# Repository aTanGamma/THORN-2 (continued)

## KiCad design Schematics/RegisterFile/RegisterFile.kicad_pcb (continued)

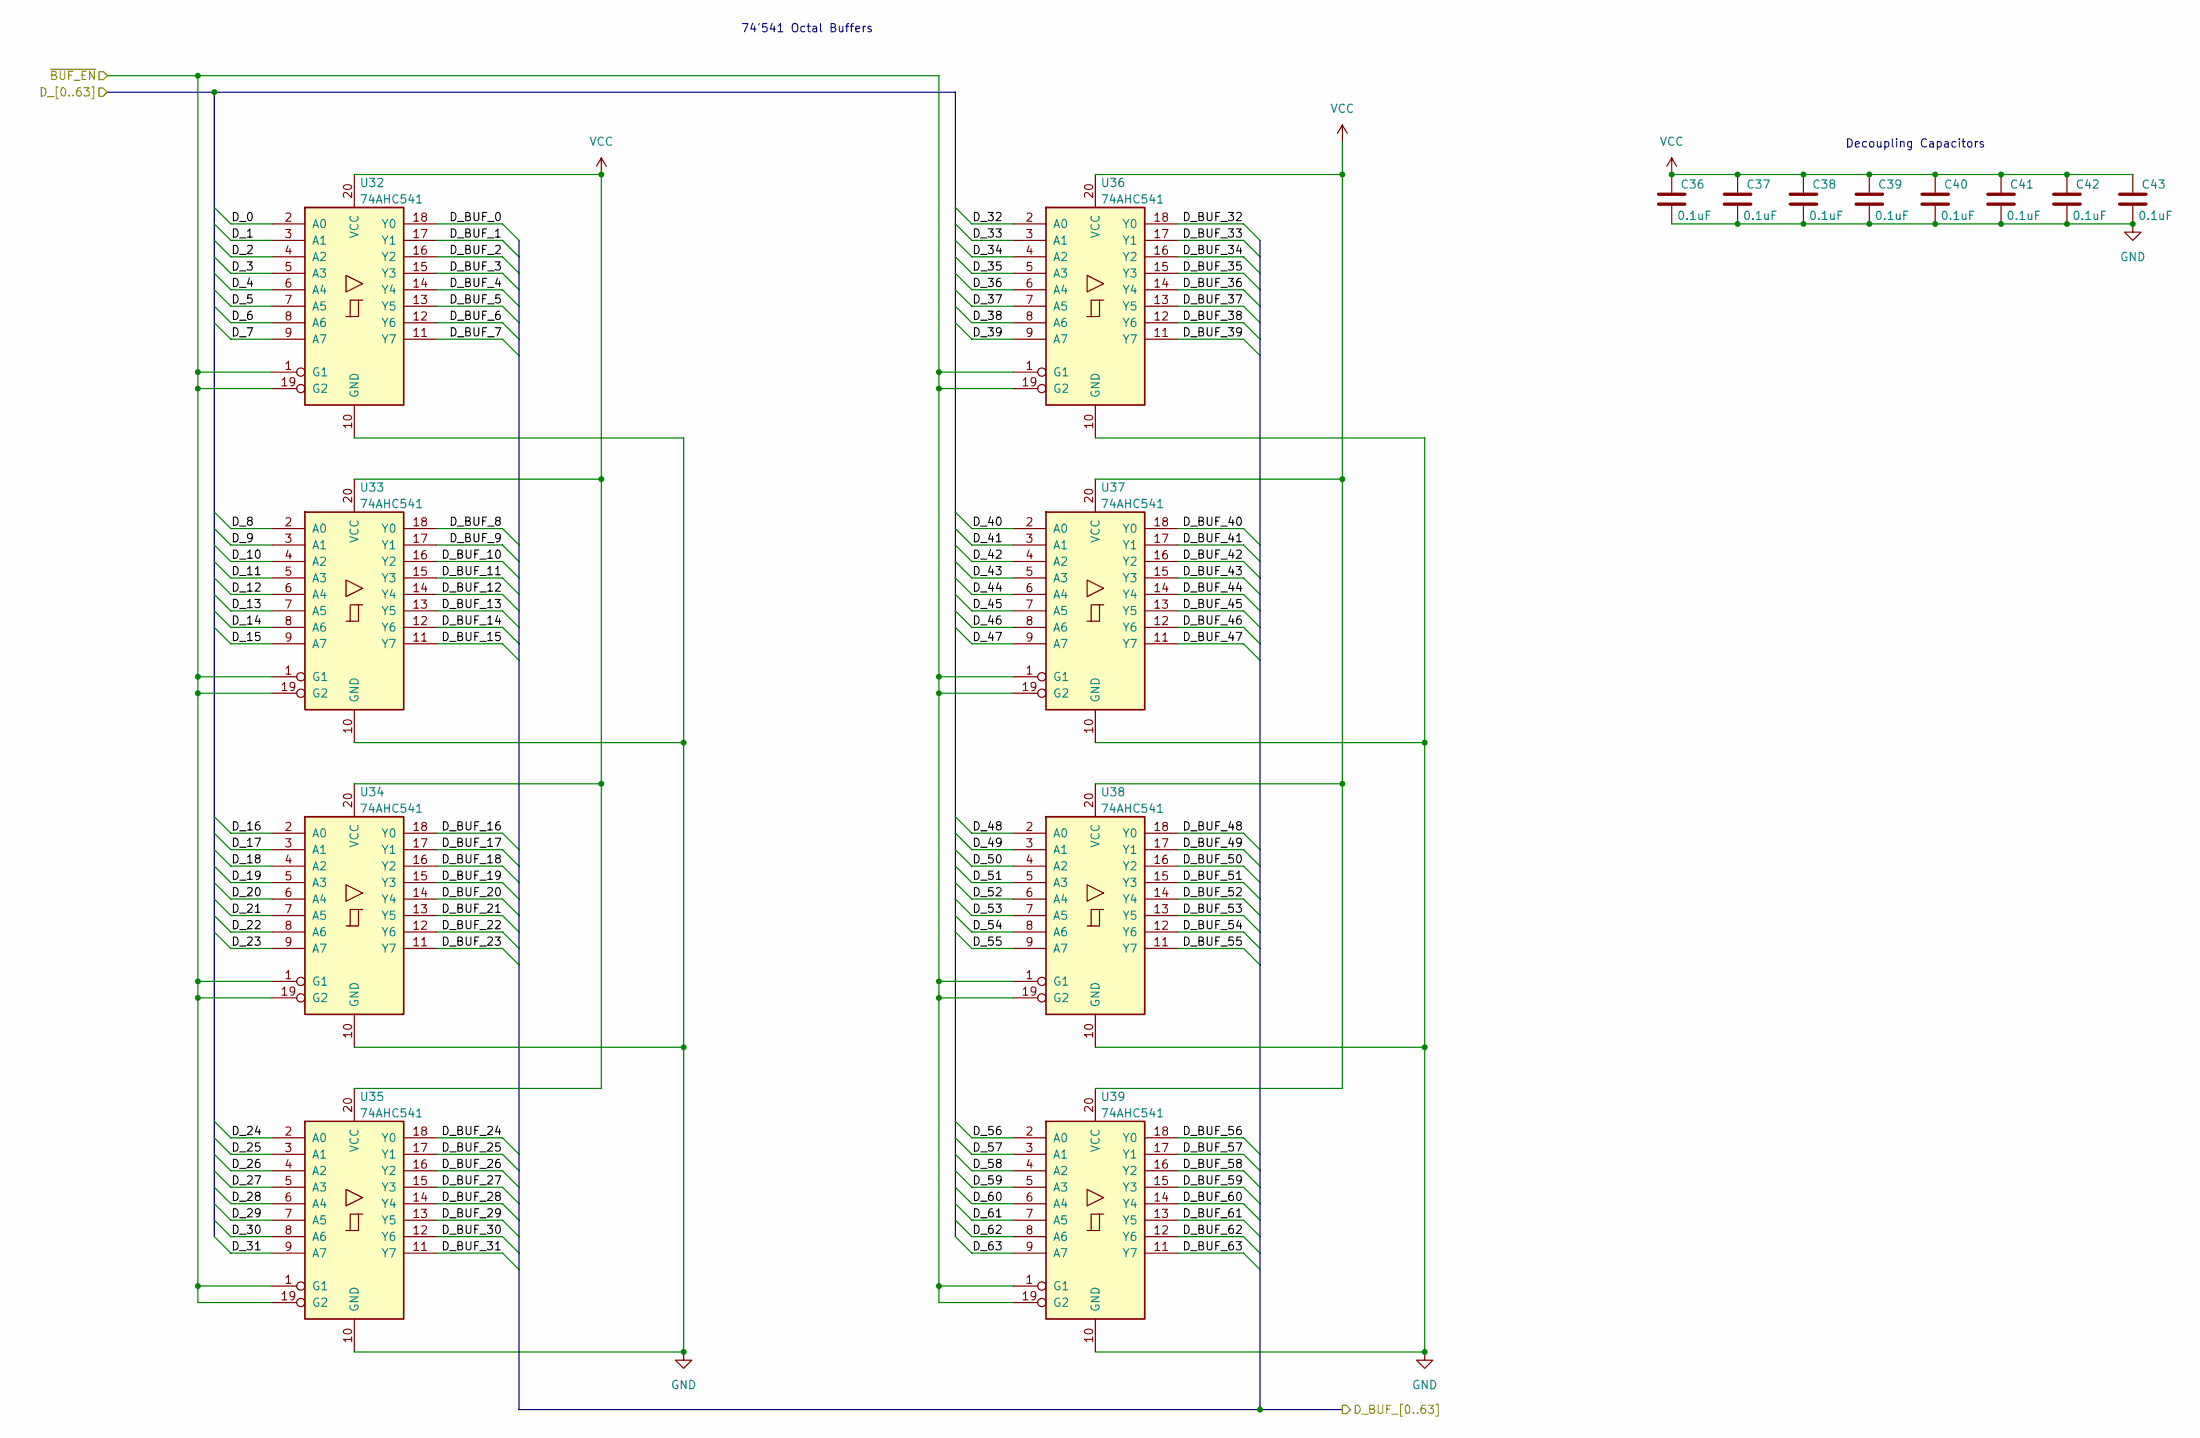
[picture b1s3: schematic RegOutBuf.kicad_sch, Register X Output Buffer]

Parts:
C36, C37, C38, C39, C40, C41, C42, C43: 0.1uF; C_1206_3216Metric
U32, U33, U34, U35, U36, U37, U38, U39: 74AHC541; TSSOP-20_4.4x6.5mm_P0.65mm

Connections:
/Register_RAM_Bank_Y/Data_0: U32.18 (Y0); also elsewhere on the board
/Register_RAM_Bank_Y/Data_1: U32.17 (Y1); also elsewhere on the board
/Register_RAM_Bank_Y/Data_2: U32.16 (Y2); also elsewhere on the board
/Register_RAM_Bank_Y/Data_3: U32.15 (Y3); also elsewhere on the board
/Register_RAM_Bank_Y/Data_4: U32.14 (Y4); also elsewhere on the board
/Register_RAM_Bank_Y/Data_5: U32.13 (Y5); also elsewhere on the board
/Register_RAM_Bank_Y/Data_6: U32.12 (Y6); also elsewhere on the board
/Register_RAM_Bank_Y/Data_7: U32.11 (Y7); also elsewhere on the board
/Register_RAM_Bank_Y/Data_8: U33.18 (Y0); also elsewhere on the board
/Register_RAM_Bank_Y/Data_9: U33.17 (Y1); also elsewhere on the board
/Register_RAM_Bank_Y/Data_10: U33.16 (Y2); also elsewhere on the board
/Register_RAM_Bank_Y/Data_11: U33.15 (Y3); also elsewhere on the board
/Register_RAM_Bank_Y/Data_12: U33.14 (Y4); also elsewhere on the board
/Register_RAM_Bank_Y/Data_13: U33.13 (Y5); also elsewhere on the board
/Register_RAM_Bank_Y/Data_14: U33.12 (Y6); also elsewhere on the board
/Register_RAM_Bank_Y/Data_15: U33.11 (Y7); also elsewhere on the board
/Register_RAM_Bank_Y/Data_16: U34.18 (Y0); also elsewhere on the board
/Register_RAM_Bank_Y/Data_17: U34.17 (Y1); also elsewhere on the board
/Register_RAM_Bank_Y/Data_18: U34.16 (Y2); also elsewhere on the board
/Register_RAM_Bank_Y/Data_19: U34.15 (Y3); also elsewhere on the board
/Register_RAM_Bank_Y/Data_20: U34.14 (Y4); also elsewhere on the board
/Register_RAM_Bank_Y/Data_21: U34.13 (Y5); also elsewhere on the board
/Register_RAM_Bank_Y/Data_22: U34.12 (Y6); also elsewhere on the board
/Register_RAM_Bank_Y/Data_23: U34.11 (Y7); also elsewhere on the board
/Register_RAM_Bank_Y/Data_24: U35.18 (Y0); also elsewhere on the board
/Register_RAM_Bank_Y/Data_25: U35.17 (Y1); also elsewhere on the board
/Register_RAM_Bank_Y/Data_26: U35.16 (Y2); also elsewhere on the board
/Register_RAM_Bank_Y/Data_27: U35.15 (Y3); also elsewhere on the board
/Register_RAM_Bank_Y/Data_28: U35.14 (Y4); also elsewhere on the board
/Register_RAM_Bank_Y/Data_29: U35.13 (Y5); also elsewhere on the board
/Register_RAM_Bank_Y/Data_30: U35.12 (Y6); also elsewhere on the board
/Register_RAM_Bank_Y/Data_31: U35.11 (Y7); also elsewhere on the board
/Register_RAM_Bank_Y/Data_32: U36.18 (Y0); also elsewhere on the board
/Register_RAM_Bank_Y/Data_33: U36.17 (Y1); also elsewhere on the board
/Register_RAM_Bank_Y/Data_34: U36.16 (Y2); also elsewhere on the board
/Register_RAM_Bank_Y/Data_35: U36.15 (Y3); also elsewhere on the board
/Register_RAM_Bank_Y/Data_36: U36.14 (Y4); also elsewhere on the board
/Register_RAM_Bank_Y/Data_37: U36.13 (Y5); also elsewhere on the board
/Register_RAM_Bank_Y/Data_38: U36.12 (Y6); also elsewhere on the board
/Register_RAM_Bank_Y/Data_39: U36.11 (Y7); also elsewhere on the board
/Register_RAM_Bank_Y/Data_40: U37.18 (Y0); also elsewhere on the board
/Register_RAM_Bank_Y/Data_41: U37.17 (Y1); also elsewhere on the board
/Register_RAM_Bank_Y/Data_42: U37.16 (Y2); also elsewhere on the board
/Register_RAM_Bank_Y/Data_43: U37.15 (Y3); also elsewhere on the board
/Register_RAM_Bank_Y/Data_44: U37.14 (Y4); also elsewhere on the board
/Register_RAM_Bank_Y/Data_45: U37.13 (Y5); also elsewhere on the board
/Register_RAM_Bank_Y/Data_46: U37.12 (Y6); also elsewhere on the board
/Register_RAM_Bank_Y/Data_47: U37.11 (Y7); also elsewhere on the board
/Register_RAM_Bank_Y/Data_48: U38.18 (Y0); also elsewhere on the board
/Register_RAM_Bank_Y/Data_49: U38.17 (Y1); also elsewhere on the board
/Register_RAM_Bank_Y/Data_50: U38.16 (Y2); also elsewhere on the board
/Register_RAM_Bank_Y/Data_51: U38.15 (Y3); also elsewhere on the board
/Register_RAM_Bank_Y/Data_52: U38.14 (Y4); also elsewhere on the board
/Register_RAM_Bank_Y/Data_53: U38.13 (Y5); also elsewhere on the board
/Register_RAM_Bank_Y/Data_54: U38.12 (Y6); also elsewhere on the board
/Register_RAM_Bank_Y/Data_55: U38.11 (Y7); also elsewhere on the board
/Register_RAM_Bank_Y/Data_56: U39.18 (Y0); also elsewhere on the board
/Register_RAM_Bank_Y/Data_57: U39.17 (Y1); also elsewhere on the board
/Register_RAM_Bank_Y/Data_58: U39.16 (Y2); also elsewhere on the board
/Register_RAM_Bank_Y/Data_59: U39.15 (Y3); also elsewhere on the board
/Register_RAM_Bank_Y/Data_60: U39.14 (Y4); also elsewhere on the board
/Register_RAM_Bank_Y/Data_61: U39.13 (Y5); also elsewhere on the board
/Register_RAM_Bank_Y/Data_62: U39.12 (Y6); also elsewhere on the board
/Register_RAM_Bank_Y/Data_63: U39.11 (Y7); also elsewhere on the board
/WB_DATA_0: U32.2 (A0); also elsewhere on the board
/WB_DATA_1: U32.3 (A1); also elsewhere on the board
/WB_DATA_2: U32.4 (A2); also elsewhere on the board
/WB_DATA_3: U32.5 (A3); also elsewhere on the board
/WB_DATA_4: U32.6 (A4); also elsewhere on the board
/WB_DATA_5: U32.7 (A5); also elsewhere on the board
/WB_DATA_6: U32.8 (A6); also elsewhere on the board
/WB_DATA_7: U32.9 (A7); also elsewhere on the board
/WB_DATA_8: U33.2 (A0); also elsewhere on the board
/WB_DATA_9: U33.3 (A1); also elsewhere on the board
/WB_DATA_10: U33.4 (A2); also elsewhere on the board
/WB_DATA_11: U33.5 (A3); also elsewhere on the board
/WB_DATA_12: U33.6 (A4); also elsewhere on the board
/WB_DATA_13: U33.7 (A5); also elsewhere on the board
/WB_DATA_14: U33.8 (A6); also elsewhere on the board
/WB_DATA_15: U33.9 (A7); also elsewhere on the board
/WB_DATA_16: U34.2 (A0); also elsewhere on the board
/WB_DATA_17: U34.3 (A1); also elsewhere on the board
/WB_DATA_18: U34.4 (A2); also elsewhere on the board
/WB_DATA_19: U34.5 (A3); also elsewhere on the board
/WB_DATA_20: U34.6 (A4); also elsewhere on the board
/WB_DATA_21: U34.7 (A5); also elsewhere on the board
/WB_DATA_22: U34.8 (A6); also elsewhere on the board
/WB_DATA_23: U34.9 (A7); also elsewhere on the board
/WB_DATA_24: U35.2 (A0); also elsewhere on the board
/WB_DATA_25: U35.3 (A1); also elsewhere on the board
/WB_DATA_26: U35.4 (A2); also elsewhere on the board
/WB_DATA_27: U35.5 (A3); also elsewhere on the board
/WB_DATA_28: U35.6 (A4); also elsewhere on the board
/WB_DATA_29: U35.7 (A5); also elsewhere on the board
/WB_DATA_30: U35.8 (A6); also elsewhere on the board
/WB_DATA_31: U35.9 (A7); also elsewhere on the board
/WB_DATA_32: U36.2 (A0); also elsewhere on the board
/WB_DATA_33: U36.3 (A1); also elsewhere on the board
/WB_DATA_34: U36.4 (A2); also elsewhere on the board
/WB_DATA_35: U36.5 (A3); also elsewhere on the board
/WB_DATA_36: U36.6 (A4); also elsewhere on the board
/WB_DATA_37: U36.7 (A5); also elsewhere on the board
/WB_DATA_38: U36.8 (A6); also elsewhere on the board
/WB_DATA_39: U36.9 (A7); also elsewhere on the board
/WB_DATA_40: U37.2 (A0); also elsewhere on the board
/WB_DATA_41: U37.3 (A1); also elsewhere on the board
/WB_DATA_42: U37.4 (A2); also elsewhere on the board
/WB_DATA_43: U37.5 (A3); also elsewhere on the board
/WB_DATA_44: U37.6 (A4); also elsewhere on the board
/WB_DATA_45: U37.7 (A5); also elsewhere on the board
/WB_DATA_46: U37.8 (A6); also elsewhere on the board
/WB_DATA_47: U37.9 (A7); also elsewhere on the board
/WB_DATA_48: U38.2 (A0); also elsewhere on the board
/WB_DATA_49: U38.3 (A1); also elsewhere on the board
/WB_DATA_50: U38.4 (A2); also elsewhere on the board
/WB_DATA_51: U38.5 (A3); also elsewhere on the board
/WB_DATA_52: U38.6 (A4); also elsewhere on the board
/WB_DATA_53: U38.7 (A5); also elsewhere on the board
/WB_DATA_54: U38.8 (A6); also elsewhere on the board
/WB_DATA_55: U38.9 (A7); also elsewhere on the board
/WB_DATA_56: U39.2 (A0); also elsewhere on the board
/WB_DATA_57: U39.3 (A1); also elsewhere on the board
/WB_DATA_58: U39.4 (A2); also elsewhere on the board
/WB_DATA_59: U39.5 (A3); also elsewhere on the board
/WB_DATA_60: U39.6 (A4); also elsewhere on the board
/WB_DATA_61: U39.7 (A5); also elsewhere on the board
/WB_DATA_62: U39.8 (A6); also elsewhere on the board
/WB_DATA_63: U39.9 (A7); also elsewhere on the board
/~WE: U32.1 (G1), U32.19 (G2), U33.1 (G1), U33.19 (G2), U34.1 (G1), U34.19 (G2), U35.1 (G1), U35.19 (G2), U36.1 (G1), U36.19 (G2), U37.1 (G1), U37.19 (G2), U38.1 (G1), U38.19 (G2), U39.1 (G1), U39.19 (G2); also elsewhere on the board
GND: C36.2, C37.2, C38.2, C39.2, C40.2, C41.2, C42.2, C43.2, U32.10 (GND), U33.10 (GND), U34.10 (GND), U35.10 (GND), U36.10 (GND), U37.10 (GND), U38.10 (GND), U39.10 (GND); also elsewhere on the board
VCC: C36.1, C37.1, C38.1, C39.1, C40.1, C41.1, C42.1, C43.1, U32.20 (VCC), U33.20 (VCC), U34.20 (VCC), U35.20 (VCC), U36.20 (VCC), U37.20 (VCC), U38.20 (VCC), U39.20 (VCC); also elsewhere on the board

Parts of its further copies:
C44, C45, C46, C47, C48, C49, C50, C51: 0.1uF; C_1206_3216Metric
U40, U41, U42, U43, U44, U45, U46, U47: 74AHC541; TSSOP-20_4.4x6.5mm_P0.65mm

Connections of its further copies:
/REG_OUT_Y_0: U40.18 (Y0); also elsewhere on the board
/REG_OUT_Y_1: U40.17 (Y1); also elsewhere on the board
/REG_OUT_Y_2: U40.16 (Y2); also elsewhere on the board
/REG_OUT_Y_3: U40.15 (Y3); also elsewhere on the board
/REG_OUT_Y_4: U40.14 (Y4); also elsewhere on the board
/REG_OUT_Y_5: U40.13 (Y5); also elsewhere on the board
/REG_OUT_Y_6: U40.12 (Y6); also elsewhere on the board
/REG_OUT_Y_7: U40.11 (Y7); also elsewhere on the board
/REG_OUT_Y_8: U41.18 (Y0); also elsewhere on the board
/REG_OUT_Y_9: U41.17 (Y1); also elsewhere on the board
/REG_OUT_Y_10: U41.16 (Y2); also elsewhere on the board
/REG_OUT_Y_11: U41.15 (Y3); also elsewhere on the board
/REG_OUT_Y_12: U41.14 (Y4); also elsewhere on the board
/REG_OUT_Y_13: U41.13 (Y5); also elsewhere on the board
/REG_OUT_Y_14: U41.12 (Y6); also elsewhere on the board
/REG_OUT_Y_15: U41.11 (Y7); also elsewhere on the board
/REG_OUT_Y_16: U42.18 (Y0); also elsewhere on the board
/REG_OUT_Y_17: U42.17 (Y1); also elsewhere on the board
/REG_OUT_Y_18: U42.16 (Y2); also elsewhere on the board
/REG_OUT_Y_19: U42.15 (Y3); also elsewhere on the board
/REG_OUT_Y_20: U42.14 (Y4); also elsewhere on the board
/REG_OUT_Y_21: U42.13 (Y5); also elsewhere on the board
/REG_OUT_Y_22: U42.12 (Y6); also elsewhere on the board
/REG_OUT_Y_23: U42.11 (Y7); also elsewhere on the board
/REG_OUT_Y_24: U43.18 (Y0); also elsewhere on the board
/REG_OUT_Y_25: U43.17 (Y1); also elsewhere on the board
/REG_OUT_Y_26: U43.16 (Y2); also elsewhere on the board
/REG_OUT_Y_27: U43.15 (Y3); also elsewhere on the board
/REG_OUT_Y_28: U43.14 (Y4); also elsewhere on the board
/REG_OUT_Y_29: U43.13 (Y5); also elsewhere on the board
/REG_OUT_Y_30: U43.12 (Y6); also elsewhere on the board
/REG_OUT_Y_31: U43.11 (Y7); also elsewhere on the board
/REG_OUT_Y_32: U44.18 (Y0); also elsewhere on the board
/REG_OUT_Y_33: U44.17 (Y1); also elsewhere on the board
/REG_OUT_Y_34: U44.16 (Y2); also elsewhere on the board
/REG_OUT_Y_35: U44.15 (Y3); also elsewhere on the board
/REG_OUT_Y_36: U44.14 (Y4); also elsewhere on the board
/REG_OUT_Y_37: U44.13 (Y5); also elsewhere on the board
/REG_OUT_Y_38: U44.12 (Y6); also elsewhere on the board
/REG_OUT_Y_39: U44.11 (Y7); also elsewhere on the board
/REG_OUT_Y_40: U45.18 (Y0); also elsewhere on the board
/REG_OUT_Y_41: U45.17 (Y1); also elsewhere on the board
/REG_OUT_Y_42: U45.16 (Y2); also elsewhere on the board
/REG_OUT_Y_43: U45.15 (Y3); also elsewhere on the board
/REG_OUT_Y_44: U45.14 (Y4); also elsewhere on the board
/REG_OUT_Y_45: U45.13 (Y5); also elsewhere on the board
/REG_OUT_Y_46: U45.12 (Y6); also elsewhere on the board
/REG_OUT_Y_47: U45.11 (Y7); also elsewhere on the board
/REG_OUT_Y_48: U46.18 (Y0); also elsewhere on the board
/REG_OUT_Y_49: U46.17 (Y1); also elsewhere on the board
/REG_OUT_Y_50: U46.16 (Y2); also elsewhere on the board
/REG_OUT_Y_51: U46.15 (Y3); also elsewhere on the board
/REG_OUT_Y_52: U46.14 (Y4); also elsewhere on the board
/REG_OUT_Y_53: U46.13 (Y5); also elsewhere on the board
/REG_OUT_Y_54: U46.12 (Y6); also elsewhere on the board
/REG_OUT_Y_55: U46.11 (Y7); also elsewhere on the board
/REG_OUT_Y_56: U47.18 (Y0); also elsewhere on the board
/REG_OUT_Y_57: U47.17 (Y1); also elsewhere on the board
/REG_OUT_Y_58: U47.16 (Y2); also elsewhere on the board
/REG_OUT_Y_59: U47.15 (Y3); also elsewhere on the board
/REG_OUT_Y_60: U47.14 (Y4); also elsewhere on the board
/REG_OUT_Y_61: U47.13 (Y5); also elsewhere on the board
/REG_OUT_Y_62: U47.12 (Y6); also elsewhere on the board
/REG_OUT_Y_63: U47.11 (Y7); also elsewhere on the board
/Register_RAM_Bank_Y/Data_0: U40.2 (A0); also elsewhere on the board
/Register_RAM_Bank_Y/Data_1: U40.3 (A1); also elsewhere on the board
/Register_RAM_Bank_Y/Data_2: U40.4 (A2); also elsewhere on the board
/Register_RAM_Bank_Y/Data_3: U40.5 (A3); also elsewhere on the board
/Register_RAM_Bank_Y/Data_4: U40.6 (A4); also elsewhere on the board
/Register_RAM_Bank_Y/Data_5: U40.7 (A5); also elsewhere on the board
/Register_RAM_Bank_Y/Data_6: U40.8 (A6); also elsewhere on the board
/Register_RAM_Bank_Y/Data_7: U40.9 (A7); also elsewhere on the board
/Register_RAM_Bank_Y/Data_8: U41.2 (A0); also elsewhere on the board
/Register_RAM_Bank_Y/Data_9: U41.3 (A1); also elsewhere on the board
/Register_RAM_Bank_Y/Data_10: U41.4 (A2); also elsewhere on the board
/Register_RAM_Bank_Y/Data_11: U41.5 (A3); also elsewhere on the board
/Register_RAM_Bank_Y/Data_12: U41.6 (A4); also elsewhere on the board
/Register_RAM_Bank_Y/Data_13: U41.7 (A5); also elsewhere on the board
/Register_RAM_Bank_Y/Data_14: U41.8 (A6); also elsewhere on the board
/Register_RAM_Bank_Y/Data_15: U41.9 (A7); also elsewhere on the board
/Register_RAM_Bank_Y/Data_16: U42.2 (A0); also elsewhere on the board
/Register_RAM_Bank_Y/Data_17: U42.3 (A1); also elsewhere on the board
/Register_RAM_Bank_Y/Data_18: U42.4 (A2); also elsewhere on the board
/Register_RAM_Bank_Y/Data_19: U42.5 (A3); also elsewhere on the board
/Register_RAM_Bank_Y/Data_20: U42.6 (A4); also elsewhere on the board
/Register_RAM_Bank_Y/Data_21: U42.7 (A5); also elsewhere on the board
/Register_RAM_Bank_Y/Data_22: U42.8 (A6); also elsewhere on the board
/Register_RAM_Bank_Y/Data_23: U42.9 (A7); also elsewhere on the board
/Register_RAM_Bank_Y/Data_24: U43.2 (A0); also elsewhere on the board
/Register_RAM_Bank_Y/Data_25: U43.3 (A1); also elsewhere on the board
/Register_RAM_Bank_Y/Data_26: U43.4 (A2); also elsewhere on the board
/Register_RAM_Bank_Y/Data_27: U43.5 (A3); also elsewhere on the board
/Register_RAM_Bank_Y/Data_28: U43.6 (A4); also elsewhere on the board
/Register_RAM_Bank_Y/Data_29: U43.7 (A5); also elsewhere on the board
/Register_RAM_Bank_Y/Data_30: U43.8 (A6); also elsewhere on the board
/Register_RAM_Bank_Y/Data_31: U43.9 (A7); also elsewhere on the board
/Register_RAM_Bank_Y/Data_32: U44.2 (A0); also elsewhere on the board
/Register_RAM_Bank_Y/Data_33: U44.3 (A1); also elsewhere on the board
/Register_RAM_Bank_Y/Data_34: U44.4 (A2); also elsewhere on the board
/Register_RAM_Bank_Y/Data_35: U44.5 (A3); also elsewhere on the board
/Register_RAM_Bank_Y/Data_36: U44.6 (A4); also elsewhere on the board
/Register_RAM_Bank_Y/Data_37: U44.7 (A5); also elsewhere on the board
/Register_RAM_Bank_Y/Data_38: U44.8 (A6); also elsewhere on the board
/Register_RAM_Bank_Y/Data_39: U44.9 (A7); also elsewhere on the board
/Register_RAM_Bank_Y/Data_40: U45.2 (A0); also elsewhere on the board
/Register_RAM_Bank_Y/Data_41: U45.3 (A1); also elsewhere on the board
/Register_RAM_Bank_Y/Data_42: U45.4 (A2); also elsewhere on the board
/Register_RAM_Bank_Y/Data_43: U45.5 (A3); also elsewhere on the board
/Register_RAM_Bank_Y/Data_44: U45.6 (A4); also elsewhere on the board
/Register_RAM_Bank_Y/Data_45: U45.7 (A5); also elsewhere on the board
/Register_RAM_Bank_Y/Data_46: U45.8 (A6); also elsewhere on the board
/Register_RAM_Bank_Y/Data_47: U45.9 (A7); also elsewhere on the board
/Register_RAM_Bank_Y/Data_48: U46.2 (A0); also elsewhere on the board
/Register_RAM_Bank_Y/Data_49: U46.3 (A1); also elsewhere on the board
/Register_RAM_Bank_Y/Data_50: U46.4 (A2); also elsewhere on the board
/Register_RAM_Bank_Y/Data_51: U46.5 (A3); also elsewhere on the board
/Register_RAM_Bank_Y/Data_52: U46.6 (A4); also elsewhere on the board
/Register_RAM_Bank_Y/Data_53: U46.7 (A5); also elsewhere on the board
/Register_RAM_Bank_Y/Data_54: U46.8 (A6); also elsewhere on the board
/Register_RAM_Bank_Y/Data_55: U46.9 (A7); also elsewhere on the board
/Register_RAM_Bank_Y/Data_56: U47.2 (A0); also elsewhere on the board
/Register_RAM_Bank_Y/Data_57: U47.3 (A1); also elsewhere on the board
/Register_RAM_Bank_Y/Data_58: U47.4 (A2); also elsewhere on the board
/Register_RAM_Bank_Y/Data_59: U47.5 (A3); also elsewhere on the board
/Register_RAM_Bank_Y/Data_60: U47.6 (A4); also elsewhere on the board
/Register_RAM_Bank_Y/Data_61: U47.7 (A5); also elsewhere on the board
/Register_RAM_Bank_Y/Data_62: U47.8 (A6); also elsewhere on the board
/Register_RAM_Bank_Y/Data_63: U47.9 (A7); also elsewhere on the board
/~BUF_EN_Y: U40.1 (G1), U40.19 (G2), U41.1 (G1), U41.19 (G2), U42.1 (G1), U42.19 (G2), U43.1 (G1), U43.19 (G2), U44.1 (G1), U44.19 (G2), U45.1 (G1), U45.19 (G2), U46.1 (G1), U46.19 (G2), U47.1 (G1), U47.19 (G2); also elsewhere on the board
GND: C44.2, C45.2, C46.2, C47.2, C48.2, C49.2, C50.2, C51.2, U40.10 (GND), U41.10 (GND), U42.10 (GND), U43.10 (GND), U44.10 (GND), U45.10 (GND), U46.10 (GND), U47.10 (GND); also elsewhere on the board
VCC: C44.1, C45.1, C46.1, C47.1, C48.1, C49.1, C50.1, C51.1, U40.20 (VCC), U41.20 (VCC), U42.20 (VCC), U43.20 (VCC), U44.20 (VCC), U45.20 (VCC), U46.20 (VCC), U47.20 (VCC); also elsewhere on the board

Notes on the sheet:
Decoupling Capacitors
74'541 Octal Buffers

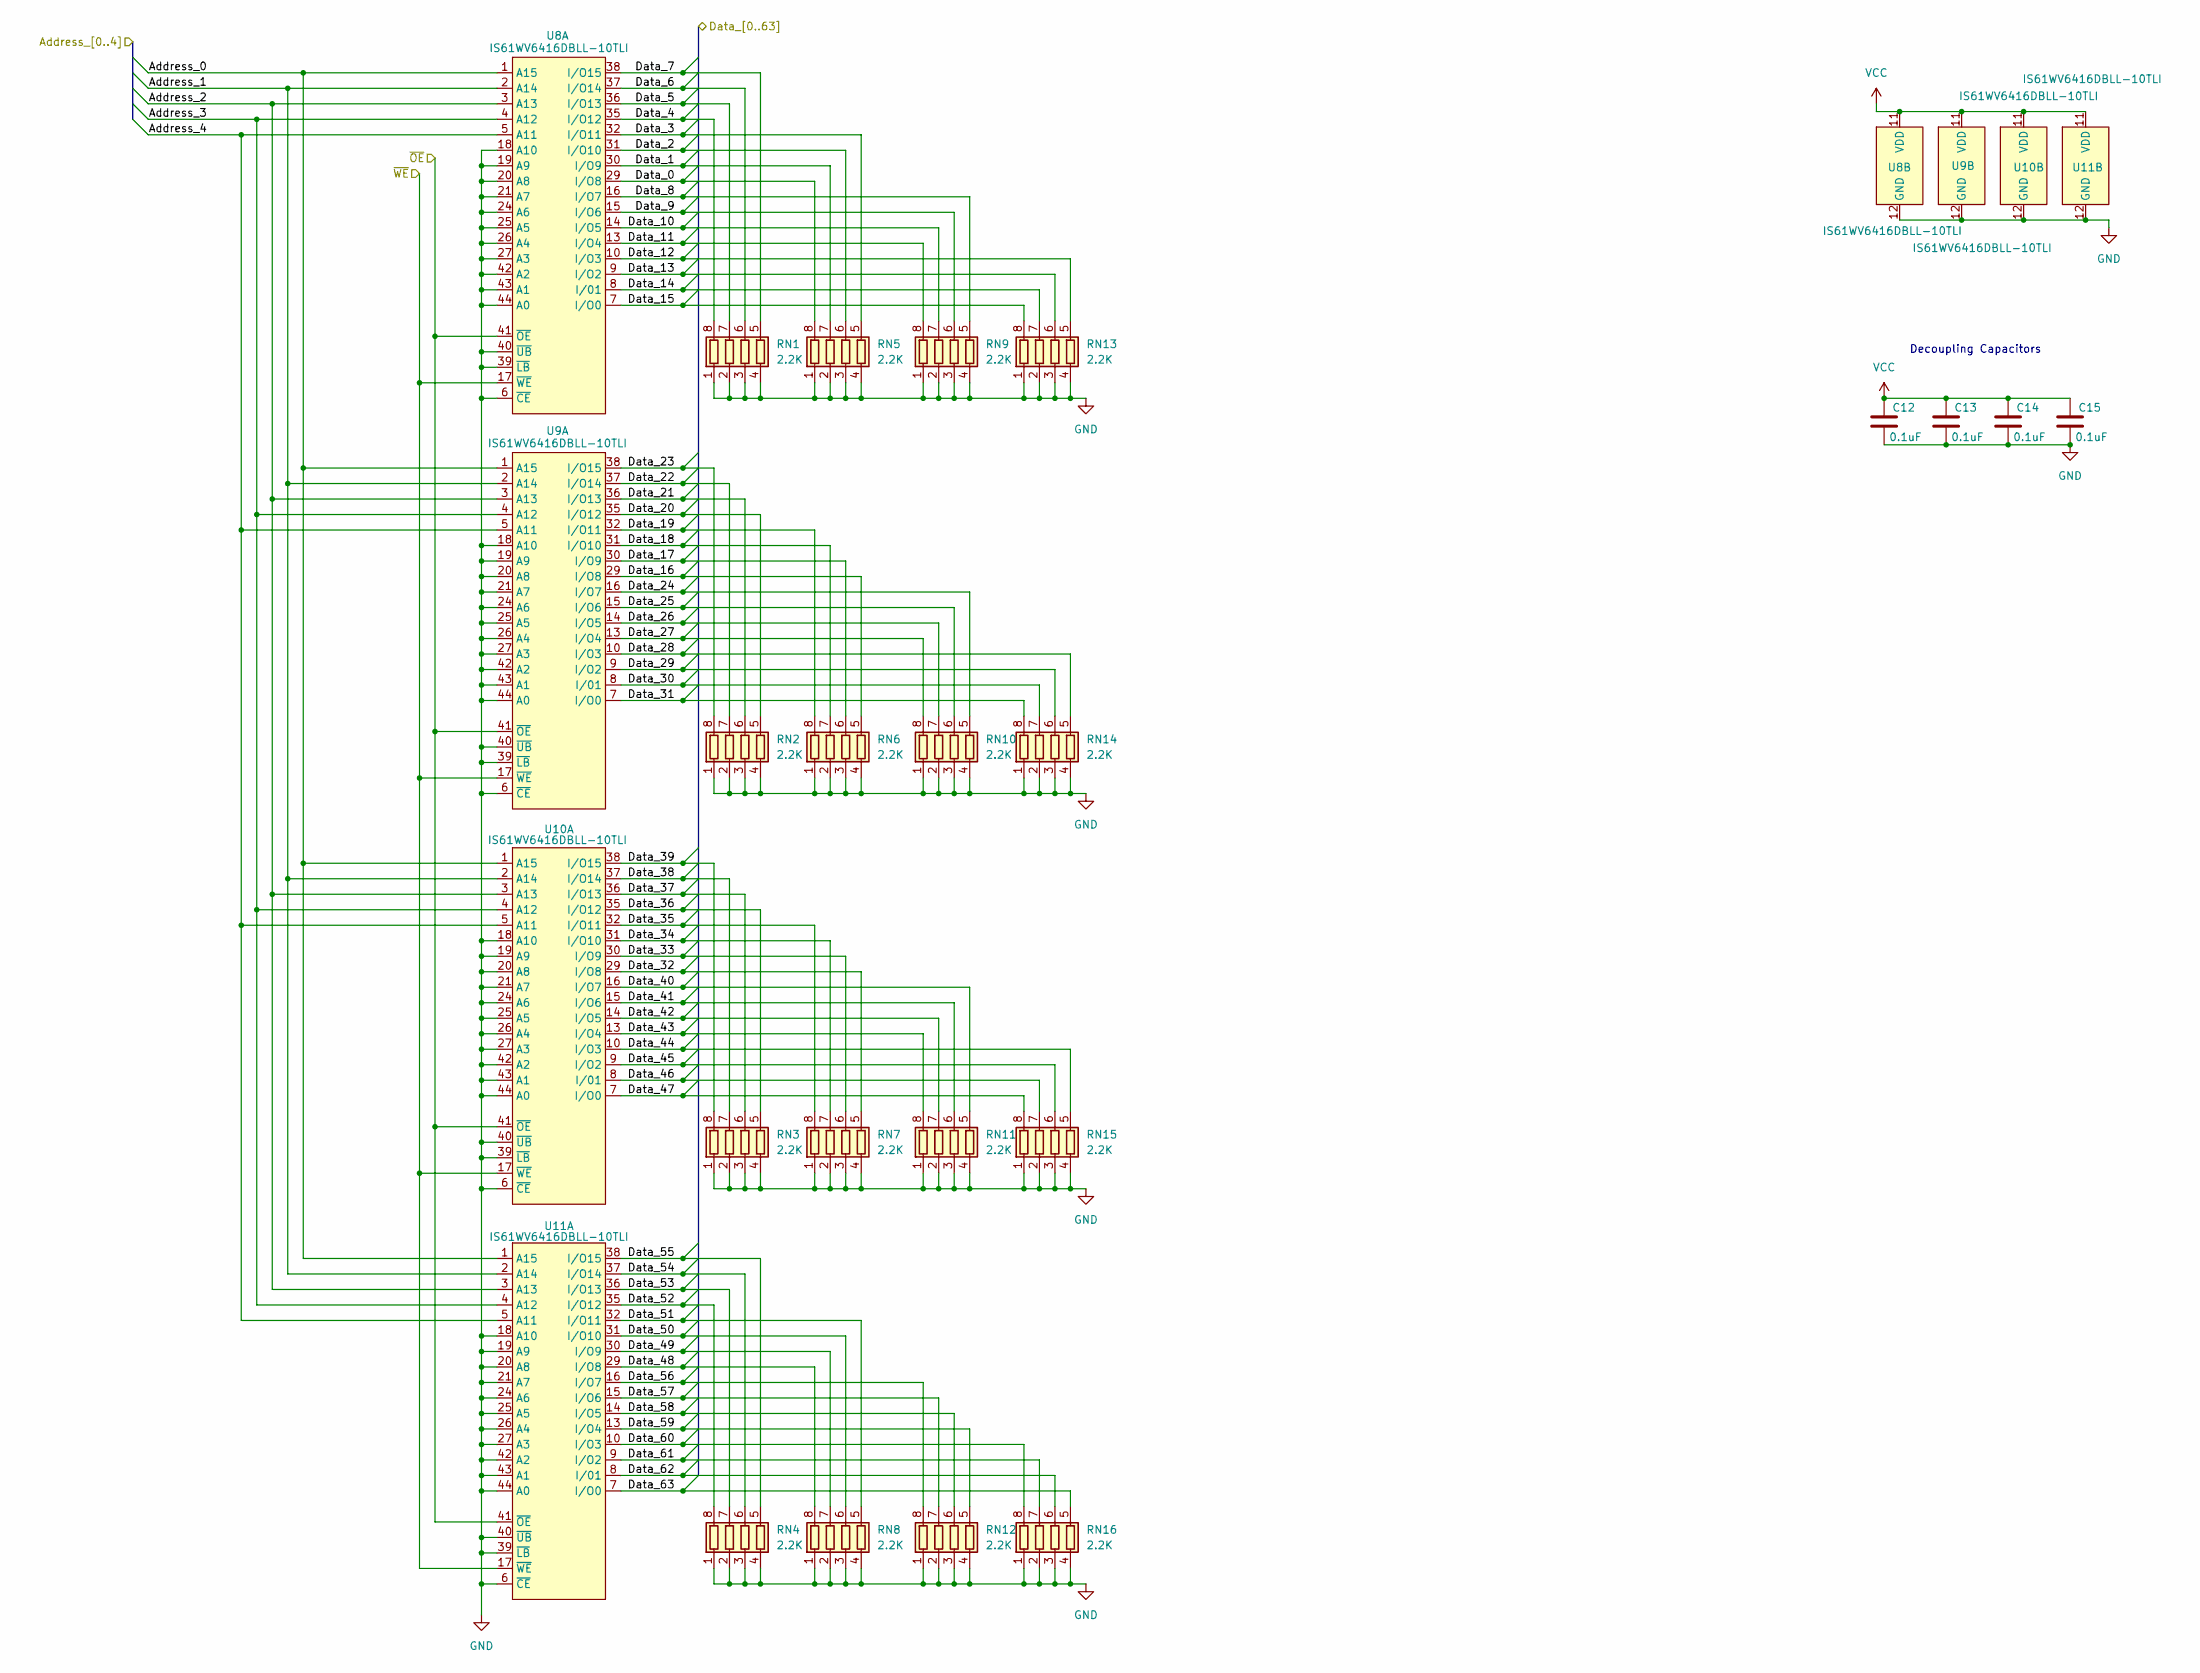
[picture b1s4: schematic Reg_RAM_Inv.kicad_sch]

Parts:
C12, C13, C14, C15: 0.1uF; C_1206_3216Metric
RN1, RN2, RN3, RN4, RN5, RN6, RN7, RN8, RN9, RN10, RN11, RN12, RN13, RN14, RN15, RN16: 2.2K; R_Array_Convex_4x0603
U8, U9, U10, U11: IS61WV6416DBLL-10TLI; TSOP-II-44_10.16x18.41mm_P0.8mm

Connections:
/Register_RAM_Bank X/Data_0: RN5.8 (R1.2), U8.29 (I/O8); also elsewhere on the board
/Register_RAM_Bank X/Data_1: RN5.7 (R2.2), U8.30 (I/O9); also elsewhere on the board
/Register_RAM_Bank X/Data_2: RN5.6 (R3.2), U8.31 (I/O10); also elsewhere on the board
/Register_RAM_Bank X/Data_3: RN5.5 (R4.2), U8.32 (I/O11); also elsewhere on the board
/Register_RAM_Bank X/Data_4: RN1.8 (R1.2), U8.35 (I/O12); also elsewhere on the board
/Register_RAM_Bank X/Data_5: RN1.7 (R2.2), U8.36 (I/O13); also elsewhere on the board
/Register_RAM_Bank X/Data_6: RN1.6 (R3.2), U8.37 (I/O14); also elsewhere on the board
/Register_RAM_Bank X/Data_7: RN1.5 (R4.2), U8.38 (I/O15); also elsewhere on the board
/Register_RAM_Bank X/Data_8: RN9.5 (R4.2), U8.16 (I/O7); also elsewhere on the board
/Register_RAM_Bank X/Data_9: RN9.6 (R3.2), U8.15 (I/O6); also elsewhere on the board
/Register_RAM_Bank X/Data_10: RN9.7 (R2.2), U8.14 (I/O5); also elsewhere on the board
/Register_RAM_Bank X/Data_11: RN9.8 (R1.2), U8.13 (I/O4); also elsewhere on the board
/Register_RAM_Bank X/Data_12: RN13.5 (R4.2), U8.10 (I/O3); also elsewhere on the board
/Register_RAM_Bank X/Data_13: RN13.6 (R3.2), U8.9 (I/O2); also elsewhere on the board
/Register_RAM_Bank X/Data_14: RN13.7 (R2.2), U8.8 (I/01); also elsewhere on the board
/Register_RAM_Bank X/Data_15: RN13.8 (R1.2), U8.7 (I/O0); also elsewhere on the board
/Register_RAM_Bank X/Data_16: RN6.5 (R4.2), U9.29 (I/O8); also elsewhere on the board
/Register_RAM_Bank X/Data_17: RN6.6 (R3.2), U9.30 (I/O9); also elsewhere on the board
/Register_RAM_Bank X/Data_18: RN6.7 (R2.2), U9.31 (I/O10); also elsewhere on the board
/Register_RAM_Bank X/Data_19: RN6.8 (R1.2), U9.32 (I/O11); also elsewhere on the board
/Register_RAM_Bank X/Data_20: RN2.5 (R4.2), U9.35 (I/O12); also elsewhere on the board
/Register_RAM_Bank X/Data_21: RN2.6 (R3.2), U9.36 (I/O13); also elsewhere on the board
/Register_RAM_Bank X/Data_22: RN2.7 (R2.2), U9.37 (I/O14); also elsewhere on the board
/Register_RAM_Bank X/Data_23: RN2.8 (R1.2), U9.38 (I/O15); also elsewhere on the board
/Register_RAM_Bank X/Data_24: RN10.5 (R4.2), U9.16 (I/O7); also elsewhere on the board
/Register_RAM_Bank X/Data_25: RN10.6 (R3.2), U9.15 (I/O6); also elsewhere on the board
/Register_RAM_Bank X/Data_26: RN10.7 (R2.2), U9.14 (I/O5); also elsewhere on the board
/Register_RAM_Bank X/Data_27: RN10.8 (R1.2), U9.13 (I/O4); also elsewhere on the board
/Register_RAM_Bank X/Data_28: RN14.5 (R4.2), U9.10 (I/O3); also elsewhere on the board
/Register_RAM_Bank X/Data_29: RN14.6 (R3.2), U9.9 (I/O2); also elsewhere on the board
/Register_RAM_Bank X/Data_30: RN14.7 (R2.2), U9.8 (I/01); also elsewhere on the board
/Register_RAM_Bank X/Data_31: RN14.8 (R1.2), U9.7 (I/O0); also elsewhere on the board
/Register_RAM_Bank X/Data_32: RN7.5 (R4.2), U10.29 (I/O8); also elsewhere on the board
/Register_RAM_Bank X/Data_33: RN7.6 (R3.2), U10.30 (I/O9); also elsewhere on the board
/Register_RAM_Bank X/Data_34: RN7.7 (R2.2), U10.31 (I/O10); also elsewhere on the board
/Register_RAM_Bank X/Data_35: RN7.8 (R1.2), U10.32 (I/O11); also elsewhere on the board
/Register_RAM_Bank X/Data_36: RN3.5 (R4.2), U10.35 (I/O12); also elsewhere on the board
/Register_RAM_Bank X/Data_37: RN3.6 (R3.2), U10.36 (I/O13); also elsewhere on the board
/Register_RAM_Bank X/Data_38: RN3.7 (R2.2), U10.37 (I/O14); also elsewhere on the board
/Register_RAM_Bank X/Data_39: RN3.8 (R1.2), U10.38 (I/O15); also elsewhere on the board
/Register_RAM_Bank X/Data_40: RN11.5 (R4.2), U10.16 (I/O7); also elsewhere on the board
/Register_RAM_Bank X/Data_41: RN11.6 (R3.2), U10.15 (I/O6); also elsewhere on the board
/Register_RAM_Bank X/Data_42: RN11.7 (R2.2), U10.14 (I/O5); also elsewhere on the board
/Register_RAM_Bank X/Data_43: RN11.8 (R1.2), U10.13 (I/O4); also elsewhere on the board
/Register_RAM_Bank X/Data_44: RN15.5 (R4.2), U10.10 (I/O3); also elsewhere on the board
/Register_RAM_Bank X/Data_45: RN15.6 (R3.2), U10.9 (I/O2); also elsewhere on the board
/Register_RAM_Bank X/Data_46: RN15.7 (R2.2), U10.8 (I/01); also elsewhere on the board
/Register_RAM_Bank X/Data_47: RN15.8 (R1.2), U10.7 (I/O0); also elsewhere on the board
/Register_RAM_Bank X/Data_48: RN8.8 (R1.2), U11.29 (I/O8); also elsewhere on the board
/Register_RAM_Bank X/Data_49: RN8.7 (R2.2), U11.30 (I/O9); also elsewhere on the board
/Register_RAM_Bank X/Data_50: RN8.6 (R3.2), U11.31 (I/O10); also elsewhere on the board
/Register_RAM_Bank X/Data_51: RN8.5 (R4.2), U11.32 (I/O11); also elsewhere on the board
/Register_RAM_Bank X/Data_52: RN4.8 (R1.2), U11.35 (I/O12); also elsewhere on the board
/Register_RAM_Bank X/Data_53: RN4.7 (R2.2), U11.36 (I/O13); also elsewhere on the board
/Register_RAM_Bank X/Data_54: RN4.6 (R3.2), U11.37 (I/O14); also elsewhere on the board
/Register_RAM_Bank X/Data_55: RN4.5 (R4.2), U11.38 (I/O15); also elsewhere on the board
/Register_RAM_Bank X/Data_56: RN12.8 (R1.2), U11.16 (I/O7); also elsewhere on the board
/Register_RAM_Bank X/Data_57: RN12.7 (R2.2), U11.15 (I/O6); also elsewhere on the board
/Register_RAM_Bank X/Data_58: RN12.6 (R3.2), U11.14 (I/O5); also elsewhere on the board
/Register_RAM_Bank X/Data_59: RN12.5 (R4.2), U11.13 (I/O4); also elsewhere on the board
/Register_RAM_Bank X/Data_60: RN16.8 (R1.2), U11.10 (I/O3); also elsewhere on the board
/Register_RAM_Bank X/Data_61: RN16.7 (R2.2), U11.9 (I/O2); also elsewhere on the board
/Register_RAM_Bank X/Data_62: RN16.6 (R3.2), U11.8 (I/01); also elsewhere on the board
/Register_RAM_Bank X/Data_63: RN16.5 (R4.2), U11.7 (I/O0); also elsewhere on the board
/X_Address_0: U8.1 (A15), U9.1 (A15), U10.1 (A15), U11.1 (A15); also elsewhere on the board
/X_Address_1: U8.2 (A14), U9.2 (A14), U10.2 (A14), U11.2 (A14); also elsewhere on the board
/X_Address_2: U8.3 (A13), U9.3 (A13), U10.3 (A13), U11.3 (A13); also elsewhere on the board
/X_Address_3: U8.4 (A12), U9.4 (A12), U10.4 (A12), U11.4 (A12); also elsewhere on the board
/X_Address_4: U8.5 (A11), U9.5 (A11), U10.5 (A11), U11.5 (A11); also elsewhere on the board
/~OE_1: U8.41 (~OE), U9.41 (~OE), U10.41 (~OE), U11.41 (~OE); also elsewhere on the board
/~WE: U8.17 (~WE), U9.17 (~WE), U10.17 (~WE), U11.17 (~WE); also elsewhere on the board
GND: C12.2, C13.2, C14.2, C15.2, RN1.1 (R1.1), RN1.2 (R2.1), RN1.3 (R3.1), RN1.4 (R4.1), RN2.1 (R1.1), RN2.2 (R2.1), RN2.3 (R3.1), RN2.4 (R4.1), RN3.1 (R1.1), RN3.2 (R2.1), RN3.3 (R3.1), RN3.4 (R4.1), RN4.1 (R1.1), RN4.2 (R2.1), RN4.3 (R3.1), RN4.4 (R4.1), RN5.1 (R1.1), RN5.2 (R2.1), RN5.3 (R3.1), RN5.4 (R4.1), RN6.1 (R1.1), RN6.2 (R2.1), RN6.3 (R3.1), RN6.4 (R4.1), RN7.1 (R1.1), RN7.2 (R2.1), RN7.3 (R3.1), RN7.4 (R4.1), RN8.1 (R1.1), RN8.2 (R2.1), RN8.3 (R3.1), RN8.4 (R4.1), RN9.1 (R1.1), RN9.2 (R2.1), RN9.3 (R3.1), RN9.4 (R4.1), RN10.1 (R1.1), RN10.2 (R2.1), RN10.3 (R3.1), RN10.4 (R4.1), RN11.1 (R1.1), RN11.2 (R2.1), RN11.3 (R3.1), RN11.4 (R4.1), RN12.1 (R1.1), RN12.2 (R2.1), RN12.3 (R3.1), RN12.4 (R4.1), RN13.1 (R1.1), RN13.2 (R2.1), RN13.3 (R3.1), RN13.4 (R4.1), RN14.1 (R1.1), RN14.2 (R2.1), RN14.3 (R3.1), RN14.4 (R4.1), RN15.1 (R1.1), RN15.2 (R2.1), RN15.3 (R3.1), RN15.4 (R4.1), RN16.1 (R1.1), RN16.2 (R2.1), RN16.3 (R3.1), RN16.4 (R4.1), U8.6 (~CE), U8.12 (GND), U8.18 (A10), U8.19 (A9), U8.20 (A8), U8.21 (A7), U8.24 (A6), U8.25 (A5), U8.26 (A4), U8.27 (A3), U8.34 (GND), U8.39 (~LB), U8.40 (~UB), U8.42 (A2), U8.43 (A1), U8.44 (A0), U9.6 (~CE), U9.12 (GND), U9.18 (A10), U9.19 (A9), U9.20 (A8), U9.21 (A7), U9.24 (A6), U9.25 (A5), U9.26 (A4), U9.27 (A3), U9.34 (GND), U9.39 (~LB), U9.40 (~UB), U9.42 (A2), U9.43 (A1), U9.44 (A0), U10.6 (~CE), U10.12 (GND), U10.18 (A10), U10.19 (A9), U10.20 (A8), U10.21 (A7), U10.24 (A6), U10.25 (A5), U10.26 (A4), U10.27 (A3), U10.34 (GND), U10.39 (~LB), U10.40 (~UB), U10.42 (A2), U10.43 (A1), U10.44 (A0), U11.6 (~CE), U11.12 (GND), U11.18 (A10), U11.19 (A9), U11.20 (A8), U11.21 (A7), U11.24 (A6), U11.25 (A5), U11.26 (A4), U11.27 (A3), U11.34 (GND), U11.39 (~LB), U11.40 (~UB), U11.42 (A2), U11.43 (A1), U11.44 (A0); also elsewhere on the board
VCC: C12.1, C13.1, C14.1, C15.1, U8.11 (VDD), U8.33 (VDD), U9.11 (VDD), U9.33 (VDD), U10.11 (VDD), U10.33 (VDD), U11.11 (VDD), U11.33 (VDD); also elsewhere on the board

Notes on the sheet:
Decoupling Capacitors
